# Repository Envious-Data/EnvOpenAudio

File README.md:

# EnvOpenAudio
 An open source headphone/PC speaker project utilizing the RP2040, UDA1334A and TPA2016

## Why
I like the idea of using the RP2040 for as many things as possible and since I made my own type-c version of the pico and my phone doesnt have a 3.5mm jack its a nice little bonus... I was also thinking I could use a Tiny2040 since its even smaller than a Pro Micro style board and also has all 4 Analogue GPIOs.

## I will need help
Im not a programmer, the most I can do is scripting in bash and python, that said I need someone who can do C stuff, although there is an example for using the Rpi pico as a I2S USB Sound Card it doesnt fully function, it functions enough to use for a while but mute doesnt work and eventually USB will die off for some reason.
https://github.com/raspberrypi/pico-playground/tree/master/apps/usb_sound_card

## Contributions
Feel free to make a PR if you want to provide your own 3d modeled housings for 3d printable speakers housings or headphone cups, Ill obviously be modeling my own but its always nice to see how people approach things.

## to do list (In no particular order)
- [x] Make Functional Concept
- [ ] Firmware
- [ ] PC Speaker Housinds
- [ ] Headphone cups and band
- [ ] Custom smaller PCBs of I2S Decoder and amp.
- [x] ~~Meow at wall for 3 hours~~

## Currently working on (as of last updating this)
- 3d printed housing for speakers, small desktop style pc speakers

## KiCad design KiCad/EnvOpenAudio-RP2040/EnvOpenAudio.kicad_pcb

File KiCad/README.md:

# EnvOpenAudio

These board schematics are from adafruit, Ive imported them into KiCad and swapped the footprints to KiCad version, I will be attempting to make these boards smaller as well as removing some stuff I wont use but the good thing about this is if you want you can build this project out of such parts you can buy from adafruit or equivilent shops minus the 3d printed housings.

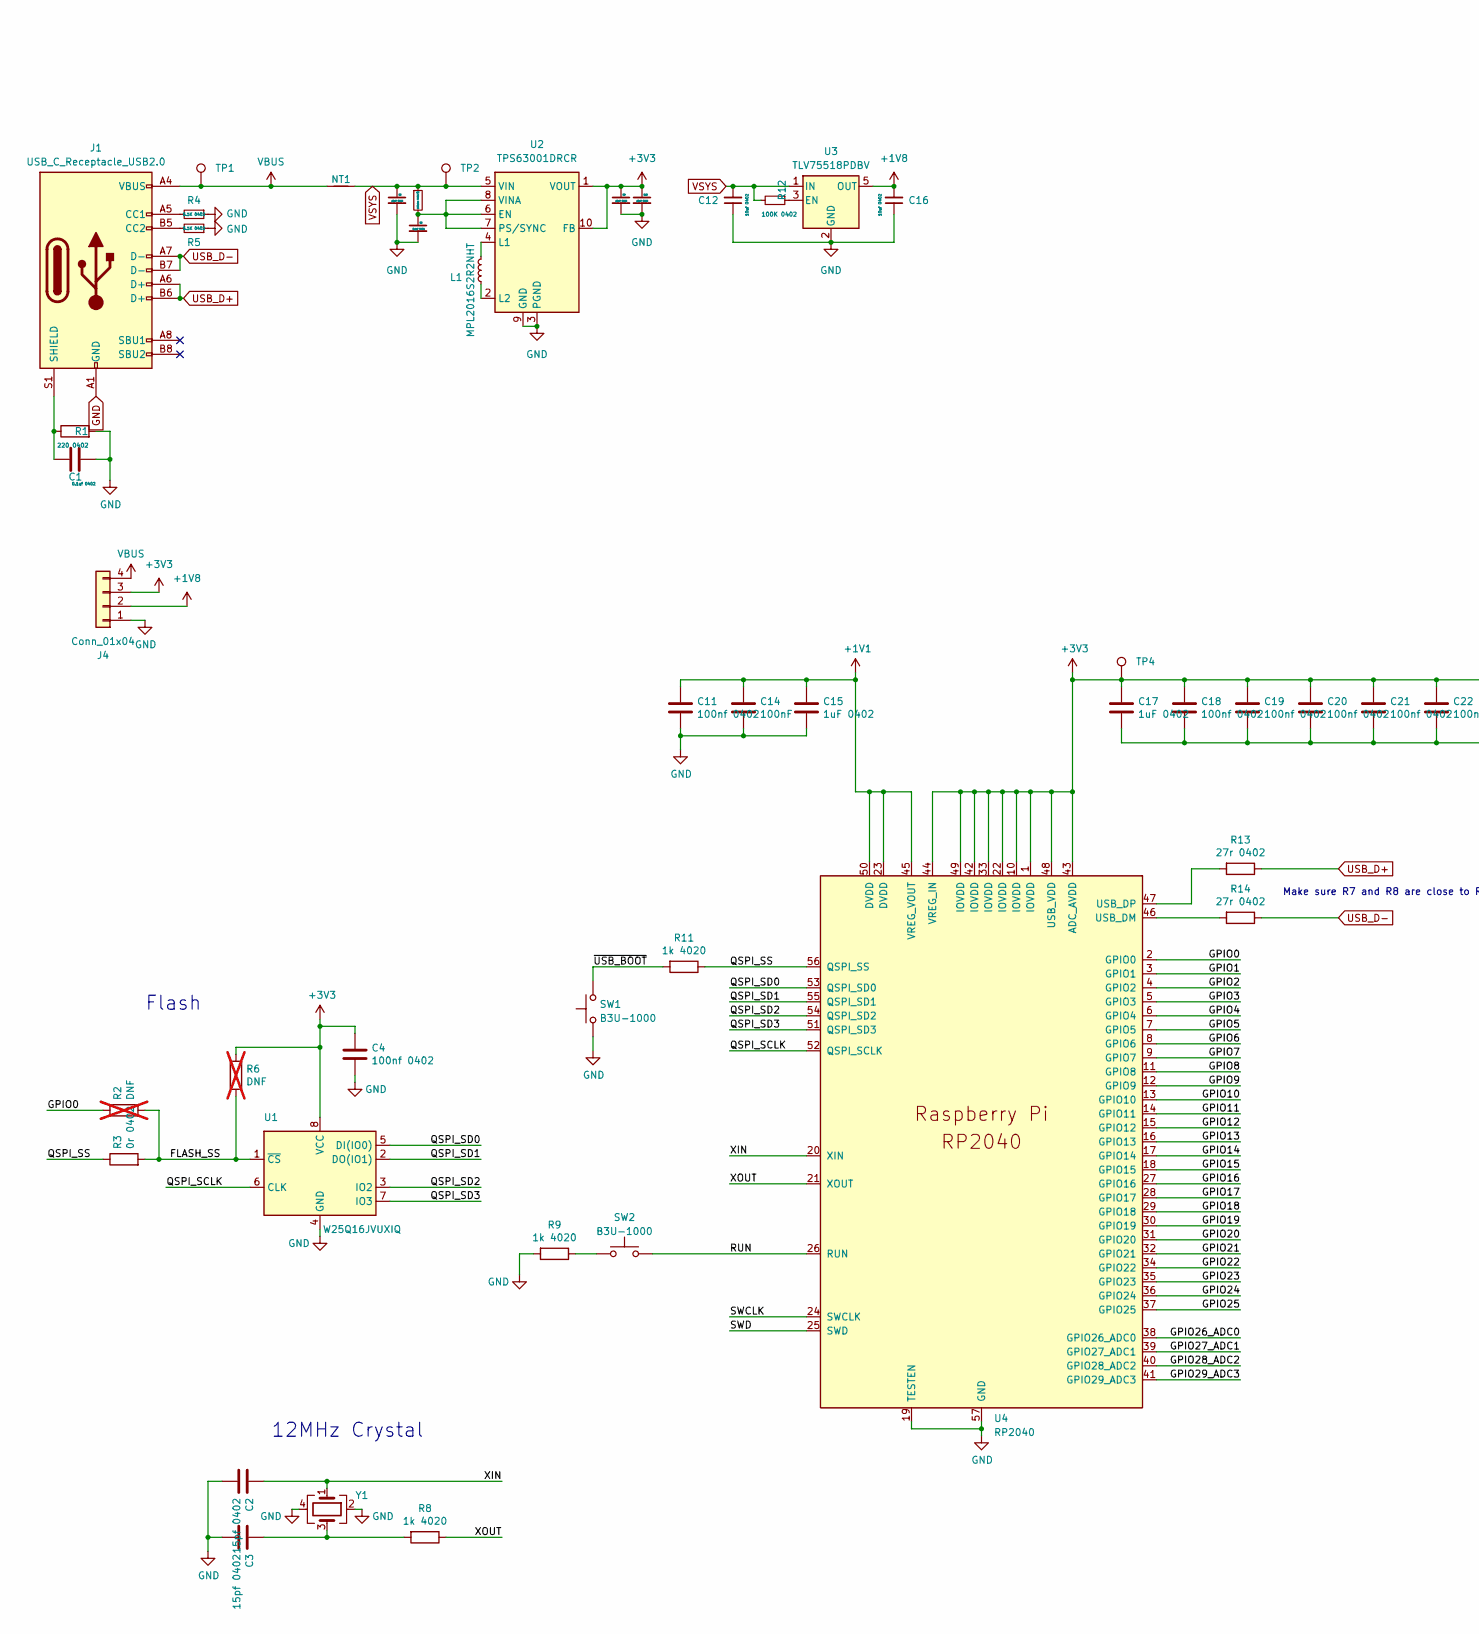
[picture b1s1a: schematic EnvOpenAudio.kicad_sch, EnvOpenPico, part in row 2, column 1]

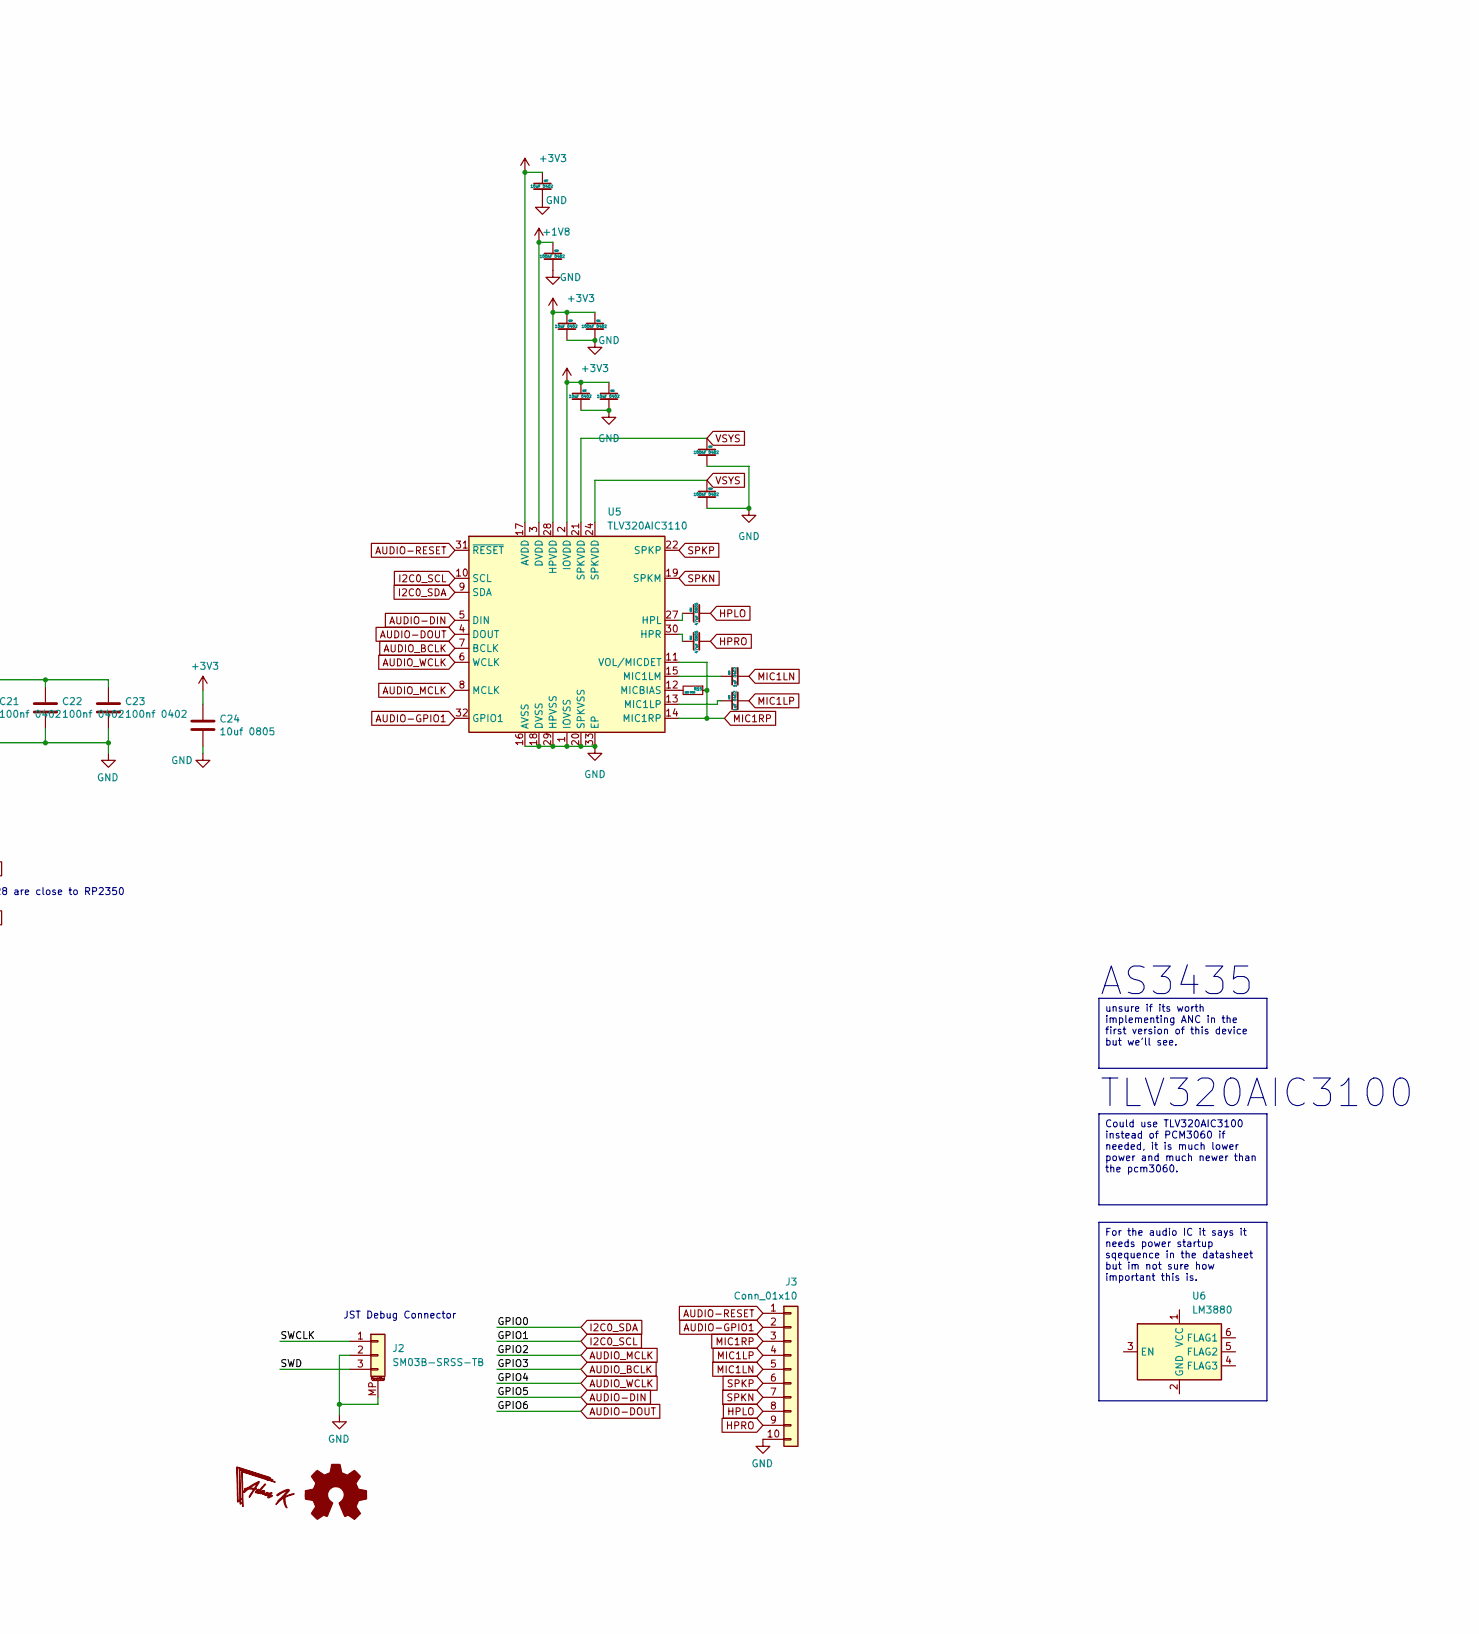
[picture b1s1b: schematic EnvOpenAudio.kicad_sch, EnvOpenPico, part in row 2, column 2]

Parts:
C1: 0.1uf 0402; C_0402_1005Metric
C2, C3: 15pf 0402; C_0402_1005Metric
C4, C11, C18, C19, C20, C21, C22, C23: 100nf 0402; C_0402_1005Metric
C5, C9, C10, C27, C28, C30, C32: 10uF 0402; C_0402_1005Metric
C6: 0.1uF 0402; C_0402_1005Metric
C12, C16: 10uf 0402; C_0402_1005Metric
C14: 100nF; C_0402_1005Metric
C15, C17, C39, C40: 1uF 0402; C_0402_1005Metric
C24: 10uf 0805; C_0805_2012Metric
C29, C31, C37, C38: 100nF 0402; C_0402_1005Metric
C35, C36: 47uF 0805; C_0805_2012Metric
J1: USB_C_Receptacle_USB2.0; USB_C_Receptacle_HRO_TYPE-C-31-M-12
J2: SM03B-SRSS-TB; JST_SH_SM03B-SRSS-TB_1x03-1MP_P1.00mm_Horizontal
J3: Conn_01x10; PinHeader_2x05_P2.54mm_Vertical
J4: Conn_01x04; PinHeader_1x04_P2.54mm_Vertical
L1: MPL2016S2R2NHT; L_0805_2012Metric
NT1: NetTie_2; NetTie-2_SMD_Pad2.0mm
R1: 220 0402; R_0402_1005Metric
R2, R6: DNF; R_0402_1005Metric; not fitted
R3: 0r 0402; R_0402_1005Metric
R4, R5: 5.1K 0402; R_0402_1005Metric
R7: 100ohm 0402; R_0402_1005Metric
R8, R9, R11: 1k 4020; R_0402_1005Metric
R12: 100K 0402; R_0402_1005Metric
R13, R14: 27r 0402; R_0402_1005Metric
R15: 22K 0402; R_0402_1005Metric
SW1, SW2: B3U-1000; SW_SPST_B3U-1000P-B
TP1, TP2, TP3, TP4: TestPoint; TestPoint_Pad_D1.0mm
U1: W25Q16JVUXIQ; SON-8-1EP_3x2mm_P0.5mm_EP1.4x1.6mm
U2: TPS63001DRCR; Texas_DRC0010J_ThermalVias
U3: TLV75518PDBV; SOT-23-5
U4: RP2040; RP2040-QFN-56
U5: TLV320AIC3110; VQFN-32-1EP_5x5mm_P0.5mm_EP3.15x3.15mm_ThermalVias
U6: LM3880; SOT-23-6
Y1: 12Mhz 2520 18pF; Crystal_SMD_2520-4Pin_2.5x2.0mm

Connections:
+1V1: C11.1, C14.1, C15.1, U4.23 (DVDD), U4.45 (VREG_VOUT), U4.50 (DVDD)
+1V8: C16.2, C29.1, J4.2, U3.5 (OUT), U5.3 (DVDD)
+3V3: C4.1, C9.1, C10.1, C17.1, C18.1, C19.1, C20.1, C21.1, C22.1, C23.1, C24.1, C27.1, C28.1, C30.1, C31.1, C32.1, J4.3, R6.1, TP4.1, U1.8 (VCC), U2.1 (VOUT), U2.10 (FB), U4.1 (IOVDD), U4.10 (IOVDD), U4.22 (IOVDD), U4.33 (IOVDD), U4.42 (IOVDD), U4.43 (ADC_AVDD), U4.44 (VREG_IN), U4.48 (USB_VDD), U4.49 (IOVDD), U5.2 (IOVDD), U5.17 (AVDD), U5.28 (HPVDD)
/FLASH_SS: R2.2, R3.2, R6.2, U1.1 (~CS)
/GPIO7: U4.9 (GPIO7)
/GPIO8: U4.11 (GPIO8)
/GPIO9: U4.12 (GPIO9)
/GPIO10: U4.13 (GPIO10)
/GPIO11: U4.14 (GPIO11)
/GPIO12: U4.15 (GPIO12)
/GPIO13: U4.16 (GPIO13)
/GPIO14: U4.17 (GPIO14)
/GPIO15: U4.18 (GPIO15)
/GPIO16: U4.27 (GPIO16)
/GPIO17: U4.28 (GPIO17)
/GPIO18: U4.29 (GPIO18)
/GPIO19: U4.30 (GPIO19)
/GPIO20: U4.31 (GPIO20)
/GPIO21: U4.32 (GPIO21)
/GPIO22: U4.34 (GPIO22)
/GPIO23: U4.35 (GPIO23)
/GPIO24: U4.36 (GPIO24)
/GPIO25: U4.37 (GPIO25)
/GPIO26_ADC0: U4.38 (GPIO26_ADC0)
/GPIO27_ADC1: U4.39 (GPIO27_ADC1)
/GPIO28_ADC2: U4.40 (GPIO28_ADC2)
/GPIO29_ADC3: U4.41 (GPIO29_ADC3)
/QSPI_SCLK: U1.6 (CLK), U4.52 (QSPI_SCLK)
/QSPI_SD0: U1.5 (DI(IO0)), U4.53 (QSPI_SD0)
/QSPI_SD1: U1.2 (DO(IO1)), U4.55 (QSPI_SD1)
/QSPI_SD2: U1.3 (IO2), U4.54 (QSPI_SD2)
/QSPI_SD3: U1.7 (IO3), U4.51 (QSPI_SD3)
/QSPI_SS: R3.1, R11.1, U4.56 (QSPI_SS)
/RUN: SW2.2, U4.26 (RUN)
/SWCLK: J2.1, U4.24 (SWCLK)
/SWD: J2.3, U4.25 (SWD)
/XIN: C2.1, U4.20 (XIN), Y1.1
/XOUT: R8.1, U4.21 (XOUT)
/~USB_BOOT: R11.2, SW1.2
AUDIO-DIN: U4.7 (GPIO5), U5.5 (DIN)
AUDIO-DOUT: U4.8 (GPIO6), U5.4 (DOUT)
AUDIO-GPIO1: J3.2, U5.32 (GPIO1)
AUDIO-RESET: J3.1, U5.31 (~RESET)
AUDIO_BCLK: U4.5 (GPIO3), U5.7 (BCLK)
AUDIO_MCLK: U4.4 (GPIO2), U5.8 (MCLK)
AUDIO_WCLK: U4.6 (GPIO4), U5.6 (WCLK)
GND: C1.1, C2.2, C3.2, C4.2, C5.2, C6.2, C9.2, C10.2, C11.2, C12.1, C14.2, C15.2, C16.1, C17.2, C18.2, C19.2, C20.2, C21.2, C22.2, C23.2, C24.2, C27.2, C28.2, C29.2, C30.2, C31.2, C32.2, C37.2, C38.2, J1.A1 (GND), J1.A12 (GND), J1.B1 (GND), J1.B12 (GND), J2.2, J2.MP (MountPin), J3.10, J4.1, R1.2, R4.1, R5.1, R9.2, SW1.1, U1.4 (GND), U2.3 (PGND), U2.9 (GND), U2.11 (PGND), U3.2 (GND), U4.19 (TESTEN), U4.57 (GND), U5.1 (IOVSS), U5.16 (AVSS), U5.18 (DVSS), U5.20 (SPKVSS), U5.25 (SPKVSS), U5.29 (HPVSS), U5.33 (EP), Y1.2, Y1.4
HPLO: C35.2, J3.8
HPRO: C36.2, J3.9
I2C0_SCL: U4.3 (GPIO1), U5.10 (SCL)
I2C0_SDA: R2.1, U4.2 (GPIO0), U5.9 (SDA)
MIC1LN: C39.2, J3.5
MIC1LP: C40.2, J3.4
MIC1RP: J3.3, R15.1, U5.11 (VOL/MICDET), U5.14 (MIC1RP)
unnamed: C3.1, R8.2, Y1.3
unnamed: J1.A5 (CC1), R4.2
unnamed: J1.B5 (CC2), R5.2
unnamed: C1.2, J1.S1 (SHIELD), R1.1
unnamed: R9.1, SW2.1
unnamed: C6.1, R7.2, U2.6 (EN), U2.7 (PS/SYNC), U2.8 (VINA)
unnamed: L1.1, U2.4 (L1)
unnamed: L1.2, U2.2 (L2)
unnamed: R12.1, U3.3 (EN)
unnamed: R14.2, U4.46 (USB_DM)
unnamed: R13.2, U4.47 (USB_DP)
unnamed: C35.1, U5.27 (HPL)
unnamed: C36.1, U5.30 (HPR)
unnamed: C39.1, U5.15 (MIC1LM)
unnamed: C40.1, U5.13 (MIC1LP)
unnamed: R15.2, U5.12 (MICBIAS)
SPKN: J3.7, U5.19 (SPKM), U5.23 (SPKM)
SPKP: J3.6, U5.22 (SPKP), U5.26 (SPKP)
USB_D+: J1.A6 (D+), J1.B6 (D+), R13.1
USB_D-: J1.A7 (D-), J1.B7 (D-), R14.1
VBUS: J1.A4 (VBUS), J1.A9 (VBUS), J1.B4 (VBUS), J1.B9 (VBUS), J4.4, NT1.1, TP1.1
VSYS: C5.1, C12.2, C37.1, C38.1, NT1.2, R7.1, R12.2, TP2.1, U2.5 (VIN), U3.1 (IN), U5.21 (SPKVDD), U5.24 (SPKVDD)

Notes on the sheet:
Could use TLV320AIC3100 instead of PCM3060 if needed, it is much lower power and much newer than the pcm3060.
For the audio IC it says it needs power startup sqequence in the datasheet but im not sure how important this is.
unsure if its worth implementing ANC in the first version of this device but we'll see.
AS3435
Make sure R7 and R8 are close to RP2350
JST Debug Connector
TLV320AIC3100
12MHz Crystal
Flash

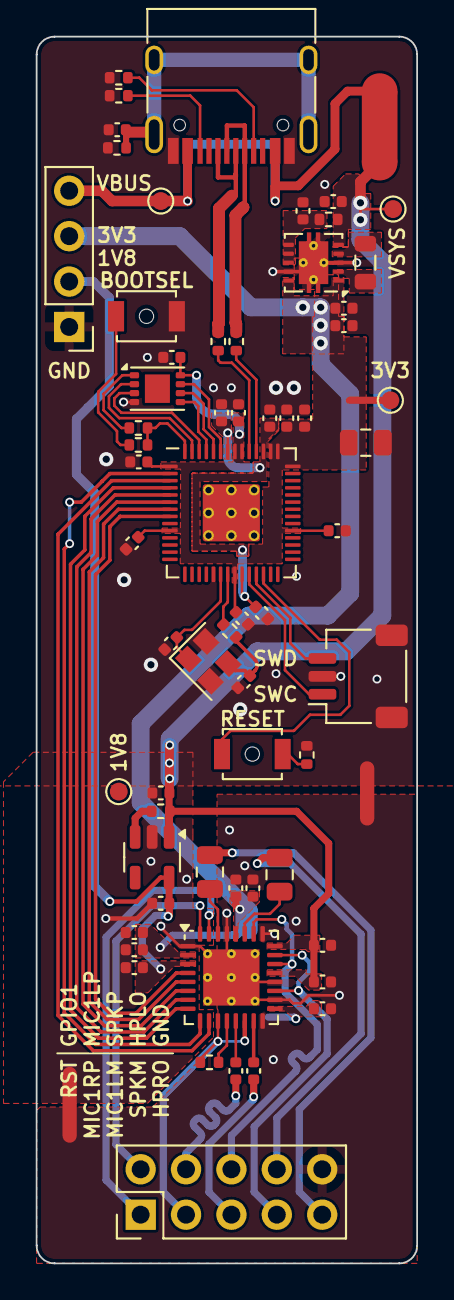
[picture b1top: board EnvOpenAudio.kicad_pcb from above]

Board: 2 copper layers, 21.3 x 68.7 mm, 63 parts (0 on the bottom side), 53 nets.

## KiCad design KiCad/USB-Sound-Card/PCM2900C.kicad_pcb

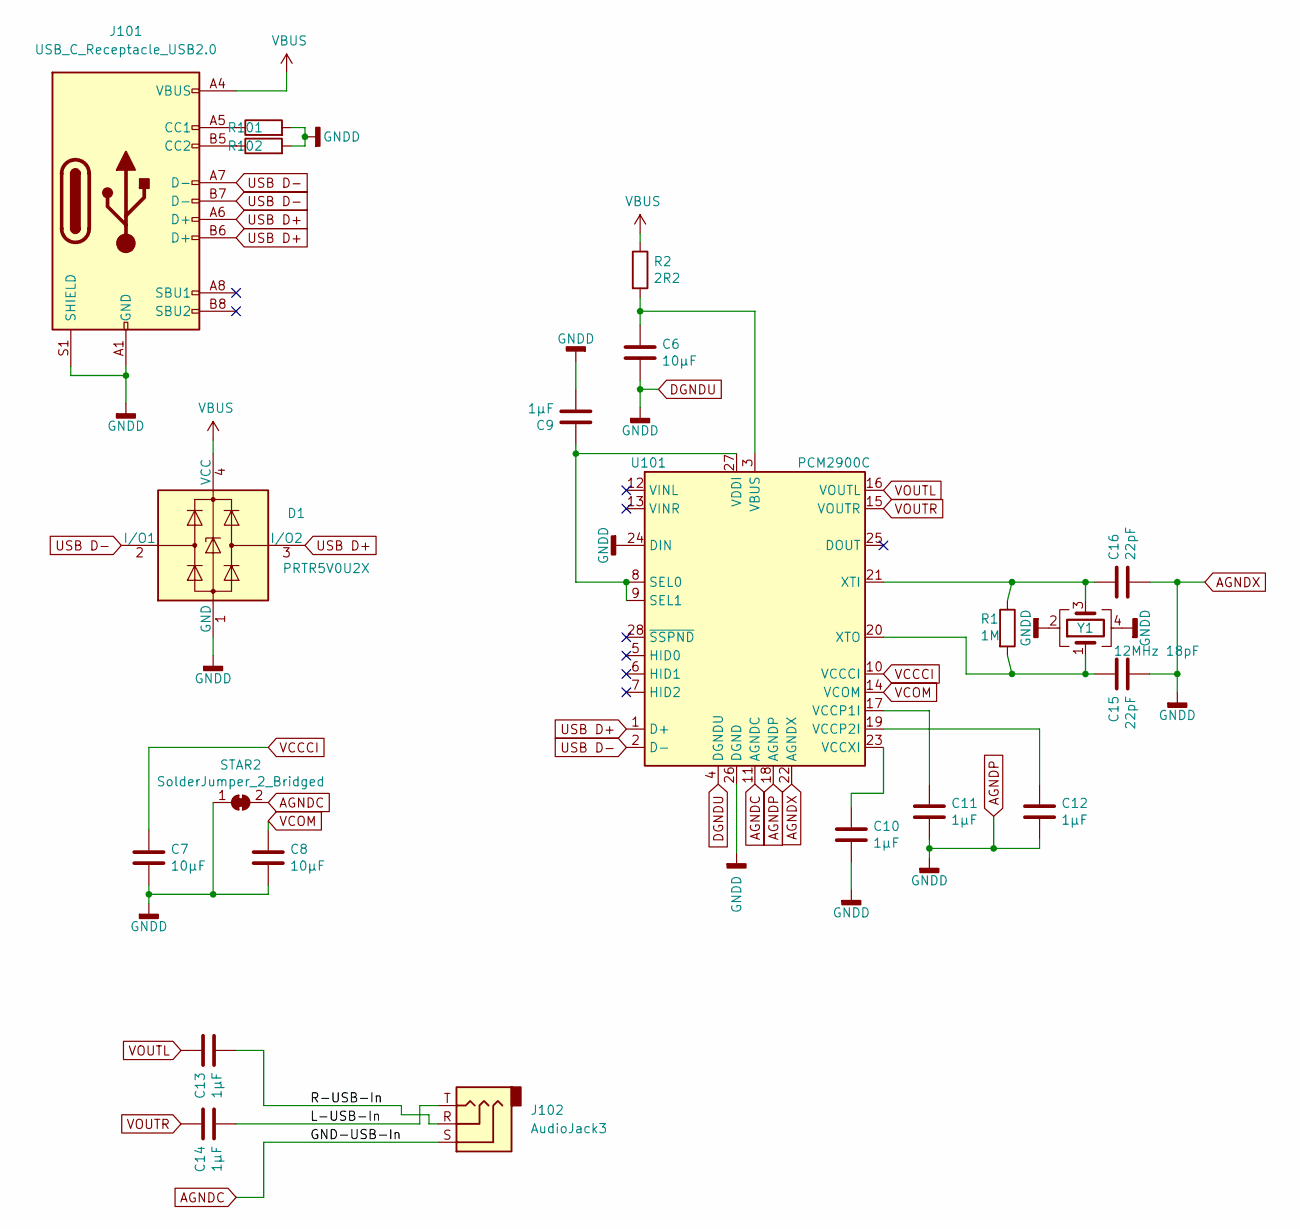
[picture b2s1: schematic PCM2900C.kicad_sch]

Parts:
C6, C7, C8: 10µF; C_0402_1005Metric
C9, C10, C11, C12, C13, C14: 1µF; C_0402_1005Metric
C15, C16: 22pF; C_0402_1005Metric
D1: PRTR5V0U2X; SOT-143
J101: USB_C_Receptacle_USB2.0; USB_C_Receptacle_HRO_TYPE-C-31-M-12
J102: AudioJack3; Jack_3.5mm_CUI_SJ1-3523N_Horizontal
R1: 1M; R_0402_1005Metric
R2: 2R2; R_0402_1005Metric
R101, R102: 5.1K 0805; R_0402_1005Metric
STAR2: SolderJumper_2_Bridged; SolderJumper-2_P1.3mm_Bridged_RoundedPad1.0x1.5mm
U101: PCM2900C; SSOP-28_5.3x10.2mm_P0.65mm
Y1: 12MHz 18pF; Crystal_SMD_3225-4Pin_3.2x2.5mm

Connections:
/L-USB-In: C14.2, J102.T
/R-USB-In: C13.2, J102.R
AGNDC: J102.S, STAR2.2 (B), U101.11 (AGNDC)
AGNDP: C6.2, C7.2, C8.2, C9.2, C10.2, C11.2, C12.2, C15.2, C16.2, D1.1 (GND), J101.A1 (GND), J101.A12 (GND), J101.B1 (GND), J101.B12 (GND), J101.S1 (SHIELD), R101.2, R102.2, STAR2.1 (A), U101.4 (DGNDU), U101.18 (AGNDP), U101.22 (AGNDX), U101.24 (DIN), U101.26 (DGND), Y1.2, Y1.4
unnamed: C6.1, R2.2, U101.3 (VBUS)
unnamed: C9.1, U101.8 (SEL0), U101.9 (SEL1), U101.27 (VDDI)
unnamed: C10.1, U101.23 (VCCXI)
unnamed: C11.1, U101.17 (VCCP1I)
unnamed: C12.1, U101.19 (VCCP2I)
unnamed: C15.1, R1.2, U101.20 (XTO), Y1.1
unnamed: C16.1, R1.1, U101.21 (XTI), Y1.3
unnamed: J101.A5 (CC1), R101.1
unnamed: J101.B5 (CC2), R102.1
USB D+: D1.3 (I/O2), J101.A6 (D+), J101.B6 (D+), U101.1 (D+)
USB D-: D1.2 (I/O1), J101.A7 (D-), J101.B7 (D-), U101.2 (D-)
VBUS: D1.4 (VCC), J101.A4 (VBUS), J101.A9 (VBUS), J101.B4 (VBUS), J101.B9 (VBUS), R2.1
VCCCI: C7.1, U101.10 (VCCCI)
VCOM: C8.1, U101.14 (VCOM)
VOUTL: C13.1, U101.16 (VOUTL)
VOUTR: C14.1, U101.15 (VOUTR)

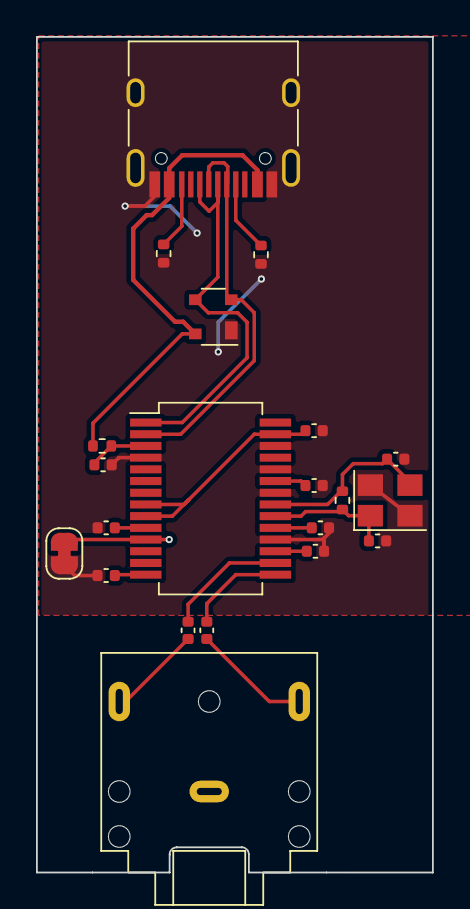
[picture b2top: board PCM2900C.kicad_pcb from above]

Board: 2 copper layers, 22.0 x 46.4 mm, 21 parts (0 on the bottom side), 20 nets.

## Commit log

2022-01-26 added files and more content to readmes
2022-01-26 started swapping symbols from eagle import to KiCad
2022-02-18 converted TPA2016D2 schematic to kicad symbols
2022-02-18 updated READMEs a tiny bit.
2022-02-19 started work on combining the two schematics
2022-03-24 modified schematic symbol to be a bit nicer
2022-06-10 actually combined both board schematics, need to do more tho
2022-06-21 more bits
2022-06-21 forgot commit one file
2022-06-25 hastily slapped together pcb
2022-06-26 added some amps, may change
2022-10-30 some general board design progress and rearrangement, need to re-do bits of the board still
2023-09-30 prepared repo for new work
2023-09-30 added 2040 base schematic and board
2023-09-30 started work on RP2040 board
2023-09-30 added some 3d models
2023-10-09 added PCM3060, picked due to low cost.
2023-11-29 added a couple notes on ANC and alternative IC.
2023-12-08 added some stuff, dont remember lol
2024-06-03 wired up audio IC
2024-06-05 wired up majority of PCB, added headers and labels.
2024-09-11 Swapped RP2040 for RP2350A for FPU, re-did board and schematic, added labels back and naming, Github link
2024-09-12 added test pads, swapped inductors for smaller models
2024-09-15 changed some component sizes, values ,added seperate analogue ground with small stitching to digital ground.
2025-01-16 Seperated into RP2040 and RP2350 variants
2025-04-03 few small changes, still need help with firmware.
2025-04-03 attempt to implement i2s and tinyusb but it does not work.
2025-04-03 got it to a compiling state but not a working one.
2025-04-05 found out pico2 was faulty, switched to pico
